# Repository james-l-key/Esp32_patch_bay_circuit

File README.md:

# ESP32 Patch Bay - Hardware

This repository contains the hardware design files for the **ESP32 Patch Bay**, a project for dynamically reconfiguring guitar pedal signal chains. The main firmware repository can be found [here](https://github.com/phi/Esp32_patch_bay).

## Features
- **Schematic**: Designed in KiCad 9.0 (`circuit.kicad_sch`).
- **8-Pedal Support**: The design supports routing for up to 8 mono guitar pedals.
- **Audio Buffering**: Utilizes TL072 op-amps for input and output buffering to maintain signal integrity.
- **Power Isolation**: A TMA-1215D DC/DC converter generates isolated ±15V rails for the analog audio circuitry, ensuring low-noise operation.

## Hardware
The patch bay is built around the following key components:

- **Microcontroller**: ESP32-S3 (e.g., ESP32-S3-WROOM-1 module).
- **Audio Routing**:
  - CD4051B 8-channel analog multiplexers.
  - 3x TL072 dual op-amps for buffering.
- **Control**:
  - 74HC595 8-bit shift registers to control the multiplexers.
- **Power**:
  - The system is powered by a **12V DC** input.
  - Onboard regulators provide **±15V**, **+5V**, **-5V**, and **+3.3V** for all components.

For a complete list of components, please see the **Bill of Materials (BOM)** in the `docs` folder or the `HARDWARE.md` file.

## Power Requirements
- **Input Power**: The system uses an external **24V DC power supply**.
- **Isolated Dual Rails (±15V)**: Supplied by an LM7815 (+15V) and an inverting MC34063AP (-15V)
- **Regulated Rails**: Onboard linear regulators provide stable **+5V**, **-5V**, and **+3.3V** is supplied by the ESP32-s3-Devkit-C for the digital components and ESP32-S3.

## License
This project is licensed under the MIT License. See the [LICENSE](LICENSE) file for details.

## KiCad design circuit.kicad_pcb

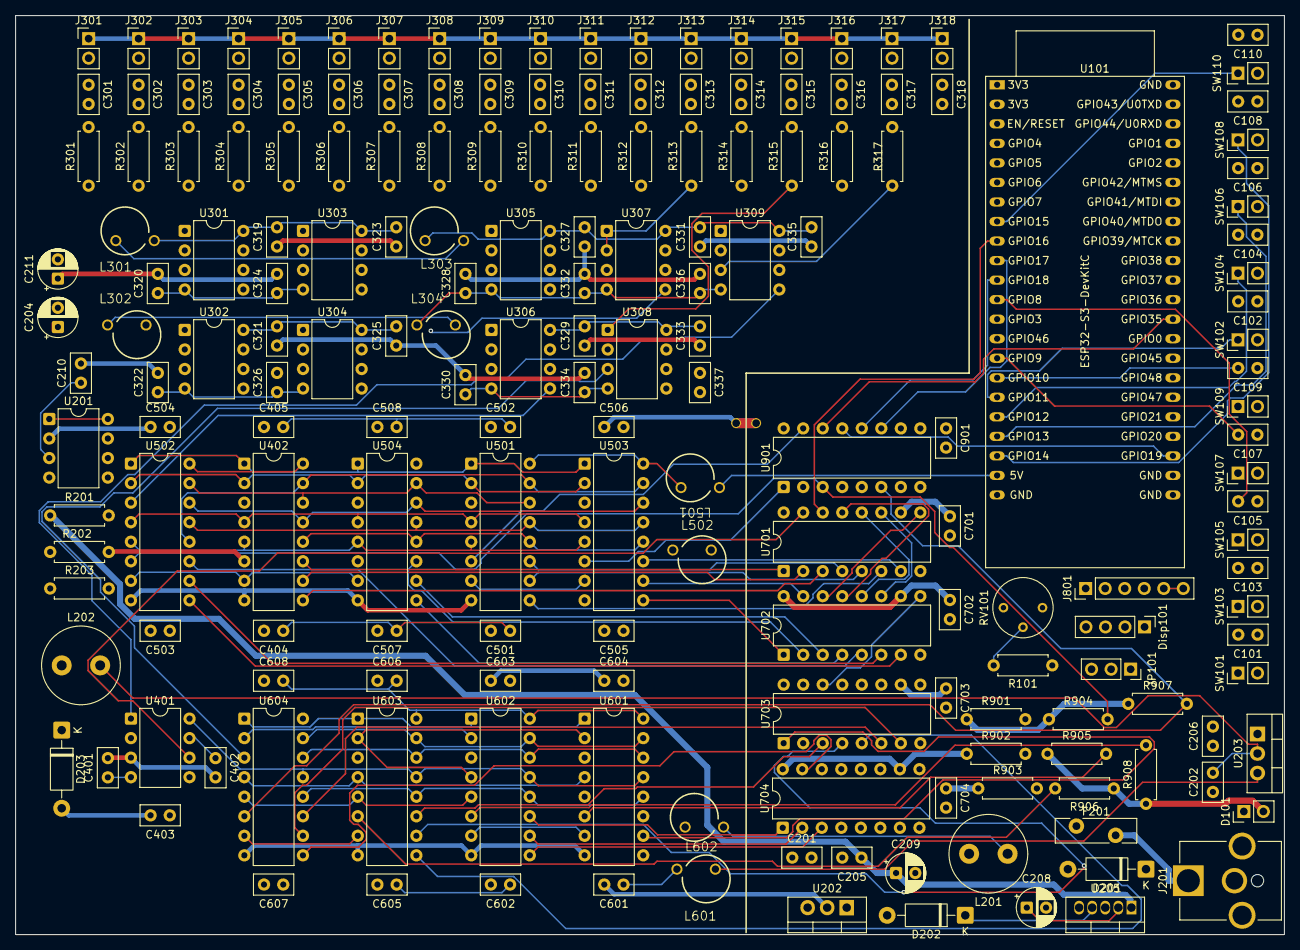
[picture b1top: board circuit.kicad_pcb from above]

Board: 4 copper layers, 165.0 x 119.5 mm, 189 parts (0 on the bottom side), 155 nets.

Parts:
C101, C102, C103, C104, C105, C106, C107, C108, C109, C110, C201, C206, C319, C320, C321, C322, C323, C324, C325, C326, C327, C328, C329, C330, C331, C332, C333, C334, C335, C336, C401, C402, C403, C404, C405, C501, C502, C503, C504, C505, C506, C507, C508, C601, C602, C603, C604, C605, C606, C607, C608, C701, C702, C703, C704, C901: 0.1uF; C_Disc_D5.0mm_W2.5mm_P2.50mm
C202, C205, C301, C302, C303, C304, C305, C306, C307, C308, C309, C310, C311, C312, C313, C314, C315, C316, C317, C318, C337: 1uF; C_Disc_D5.0mm_W2.5mm_P2.50mm
C204, C209, C211: 100uF 50v; CP_Radial_D5.0mm_P2.50mm
C208: 220uF 16v; CP_Radial_D5.0mm_P2.50mm
C210: 470pF; C_Disc_D5.0mm_W2.5mm_P2.50mm
D101: LED_PWR; PinHeader_1x02_P2.54mm_Vertical
D201, D202: 1N5822; D_DO-41_SOD81_P10.16mm_Horizontal
D203: 1N5819; D_DO-41_SOD81_P10.16mm_Horizontal
Disp101: PinHeader_1x04_P2.54mm_Vertical
F201: Polyfuse_Small; Fuse_Bourns_MF-RG500
J201: Barrel_Jack; BarrelJack_CUI_PJ-063AH_Horizontal_CircularHoles
J301: FX_R_1; Jack
J302: FX_R_2; Jack
J303: FX_R_3; Jack
J304: FX_R_4; Jack
J305: FX_R_5; Jack
J306: FX_R_6; Jack
J307: FX_R_7; Jack
J308: FX_R_8; Jack
J309: FX_S_1; Jack
J310: FX_S_2; Jack
J311: FX_S_3; Jack
J312: FX_S_4; Jack
J313: FX_S_5; Jack
J314: FX_S_6; Jack
J315: FX_S_7; Jack
J316: FX_S_8; Jack
J317: Guitar_In; Jack
J318: Amp_Out; Jack
J801: Conn_01x06_Pin; PinHeader_1x06_P2.54mm_Vertical
JP101: Jumper_3_Open; PinSocket_1x03_P2.54mm_Vertical
L201: 150uH; L_Radial_D10.0mm_P5.00mm_Fastron_07M
L202: 220uH; L_Radial_D10.0mm_P5.00mm_Fastron_07M
L301, L302, L303, L304, L501, L502, L601, L602: 600R@100Mhz; WE-UKW_74275010
NT101: NetTie_2; NetTie-2_THT_Pad1.0mm
R101: 100; R_Axial_DIN0207_L6.3mm_D2.5mm_P7.62mm_Horizontal
R201: 1.5; R_Axial_DIN0207_L6.3mm_D2.5mm_P7.62mm_Horizontal
R202: 1k; R_Axial_DIN0207_L6.3mm_D2.5mm_P7.62mm_Horizontal
R203: 11k; R_Axial_DIN0207_L6.3mm_D2.5mm_P7.62mm_Horizontal
R301, R302, R303, R304, R305, R306, R307, R308, R309, R310, R311, R312, R313, R314, R315, R316, R317, R901, R902, R903, R904, R905, R906, R907, R908: 10k; R_Axial_DIN0207_L6.3mm_D2.5mm_P7.62mm_Horizontal
RV101: 500; Potentiometer_Bourns_3339P_Vertical
SW101: Pedal_1; PinHeader_1x02_P2.54mm_Vertical
SW102: Pedal_6; PinHeader_1x02_P2.54mm_Vertical
SW103: Pedal_2; PinHeader_1x02_P2.54mm_Vertical
SW104: Pedal_7; PinHeader_1x02_P2.54mm_Vertical
SW105: Pedal_3; PinHeader_1x02_P2.54mm_Vertical
SW106: Pedal_8; PinHeader_1x02_P2.54mm_Vertical
SW107: Pedal_4; PinHeader_1x02_P2.54mm_Vertical
SW108: Program; PinHeader_1x02_P2.54mm_Vertical
SW109: Pedal_5; PinHeader_1x02_P2.54mm_Vertical
SW110: Preset; PinHeader_1x02_P2.54mm_Vertical
U101: ESP32-S3-DevKitC
U201: MC34063AP; DIP-8_W7.62mm
U202: LM7815_TO220; TO-220-3_Vertical
U203: LM7905_TO220; TO-220-3_Vertical
U205: LM2576HVT-5; TO-220-5_Vertical
U301, U302, U303, U304, U305, U306, U307, U308, U309: TL072; DIP-8_W7.62mm
U401: ADG419BN; DIP-8_W7.62mm
U402, U501, U502, U503, U504, U601, U602, U603, U604: CD4051B; DIP-16_W7.62mm
U701, U702, U703, U704, U901: 74HC595; DIP-16_W7.62mm

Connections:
3.3V: C701.1, C702.1, C703.1, C704.1, C901.1, D101.2 (A), JP101.1 (A), R901.1, R902.1, R903.1, R904.1, R905.1, R906.1, R907.1, R908.1, U101.1 (3V3), U101.2 (3V3), U701.10 (~SRCLR), U701.16 (VCC), U702.10 (~SRCLR), U702.16 (VCC), U703.10 (~SRCLR), U703.16 (VCC), U704.10 (~SRCLR), U704.16 (VCC), U901.10 (~SRCLR), U901.16 (VCC)
5.0V: J801.5, J801.6
+5V: C208.1, JP101.3 (B), L201.1, L501.1, L601.1, U101.21 (5V), U205.2 (OUT)
+5V_F: C403.1, C405.2, C502.2, C504.2, C506.2, C508.2, L501.2, U401.5 (VL), U402.16 (VDD), U501.16 (VDD), U502.16 (VDD), U503.16 (VDD), U504.16 (VDD)
+15V: C201.1, L301.2, L303.1, U202.3 (VO)
+15V_F: C319.2, C321.2, C323.2, C325.2, C401.1, L301.1, U301.8 (V+), U302.8 (V+), U303.8 (V+), U304.8 (V+), U401.4 (V+)
-5V: C206.2, L502.2, L602.2, U203.3 (VO)
-5V_F: C404.1, C501.1, C503.1, C505.1, C507.1, L502.1, U402.7 (VEE), U501.7 (VEE), U502.7 (VEE), U503.7 (VEE), U504.7 (VEE)
-15V: C202.2, C211.2, D203.1 (K), L202.2, L302.1, L304.2, R203.2, U201.1 (SwC), U201.8 (DC), U203.2 (VI)
-15V_F: C320.1, C322.1, C324.1, C326.1, C402.1, L302.2, U301.4 (V-), U302.4 (V-), U303.4 (V-), U304.4 (V-), U401.7 (V-)
/IO Routing/U701_Q0: U401.6, U701.15 (QA)
/IO Routing/U701_Q1: U402.11 (A), U701.1 (QB)
/IO Routing/U701_Q2: U402.10 (B), U701.2 (QC)
/IO Routing/U701_Q3: U402.9 (C), U701.3 (QD)
/IO Routing/U701_Q4: U501.11 (A), U701.4 (QE)
/IO Routing/U701_Q5: U501.10 (B), U701.5 (QF)
/IO Routing/U701_Q6: U501.9 (C), U701.6 (QG)
/IO Routing/U701_Q7: U503.11 (A), U701.7 (QH)
/Inhibit Registers/U901_Q0: R901.2, U501.6 (INH), U901.15 (QA)
/Inhibit Registers/U901_Q1: R902.2, U503.6 (INH), U901.1 (QB)
/Inhibit Registers/U901_Q2: R903.2, U504.6 (INH), U901.2 (QC)
/Inhibit Registers/U901_Q3: R904.2, U502.6 (INH), U901.3 (QD)
/Inhibit Registers/U901_Q4: R905.2, U601.6 (INH), U901.4 (QE)
/Inhibit Registers/U901_Q5: R906.2, U603.6 (INH), U901.5 (QF)
/Inhibit Registers/U901_Q6: R907.2, U604.6 (INH), U901.6 (QG)
/Inhibit Registers/U901_Q7: R908.2, U602.6 (INH), U901.7 (QH)
/Matrix Shift Registers/U702_Q0: U503.10 (B), U702.15 (QA)
/Matrix Shift Registers/U702_Q1: U503.9 (C), U702.1 (QB)
/Matrix Shift Registers/U702_Q2: U504.11 (A), U702.2 (QC)
/Matrix Shift Registers/U702_Q3: U504.10 (B), U702.3 (QD)
/Matrix Shift Registers/U702_Q4: U504.9 (C), U702.4 (QE)
/Matrix Shift Registers/U702_Q5: U502.11 (A), U702.5 (QF)
/Matrix Shift Registers/U702_Q6: U502.10 (B), U702.6 (QG)
/Matrix Shift Registers/U702_Q7: U502.9 (C), U702.7 (QH)
/Matrix Shift Registers/U703_Q0: U601.11 (A), U703.15 (QA)
/Matrix Shift Registers/U703_Q1: U601.10 (B), U703.1 (QB)
/Matrix Shift Registers/U703_Q2: U601.9 (C), U703.2 (QC)
/Matrix Shift Registers/U703_Q3: U603.11 (A), U703.3 (QD)
/Matrix Shift Registers/U703_Q4: U603.10 (B), U703.4 (QE)
/Matrix Shift Registers/U703_Q5: U603.9 (C), U703.5 (QF)
/Matrix Shift Registers/U703_Q6: U604.11 (A), U703.6 (QG)
/Matrix Shift Registers/U703_Q7: U604.10 (B), U703.7 (QH)
/Matrix Shift Registers/U704_Q0: U604.9 (C), U704.15 (QA)
/Matrix Shift Registers/U704_Q1: U602.11 (A), U704.1 (QB)
/Matrix Shift Registers/U704_Q2: U602.10 (B), U704.2 (QC)
/Matrix Shift Registers/U704_Q3: U602.9 (C), U704.3 (QD)
/Power/24V_RAW_1: F201.2, J201.1
/Power/24V_RAW_2: D201.2 (A), F201.1
AGND: C201.2, C204.2, C205.2, C210.2, C211.1, C319.1, C320.2, C321.1, C322.2, C323.1, C324.2, C325.1, C326.2, C327.1, C328.2, C329.1, C330.2, C331.1, C332.2, C333.1, C334.2, C335.1, C336.2, C401.2, C402.2, C403.2, C404.2, C405.1, C501.2, C502.1, C503.2, C504.1, C505.2, C506.1, C507.2, C508.1, C601.2, C602.2, C603.1, C604.1, C605.2, C606.1, C607.2, C608.1, D203.2 (A), J301.S, J302.S, J303.S, J304.S, J305.S, J306.S, J307.S, J308.S, J309.S, J310.S, J311.S, J312.S, J313.S, J314.S, J315.S, J316.S, J317.S, J318.S, L202.1, NT101.2, R202.2, U201.2 (SwE), U201.4 (GND), U202.2 (GND), U401.3 (GND), U402.6 (INH), U402.8 (VSS), U501.8 (VSS), U502.8 (VSS), U503.8 (VSS), U504.8 (VSS), U601.8 (VSS), U602.8 (VSS), U603.8 (VSS), U604.8 (VSS)
FX_R_1: U301.1 (1OUT), U301.2 (1-), U402.13 (X0), U502.14 (X1), U503.14 (X1), U504.14 (X1), U601.14 (X1), U602.14 (X1), U603.14 (X1), U604.14 (X1)
FX_R_2: U301.6 (2-), U301.7 (2OUT), U402.14 (X1), U501.14 (X1), U502.15 (X2), U504.15 (X2), U601.15 (X2), U602.15 (X2), U603.15 (X2), U604.15 (X2)
FX_R_3: U302.1 (1OUT), U302.2 (1-), U402.15 (X2), U501.15 (X2), U502.12 (X3), U503.15 (X2), U601.12 (X3), U602.12 (X3), U603.12 (X3), U604.12 (X3)
FX_R_4: U302.6 (2-), U302.7 (2OUT), U402.12 (X3), U501.12 (X3), U503.12 (X3), U504.12 (X3), U601.1 (X4), U602.1 (X4), U603.1 (X4), U604.1 (X4)
FX_R_5: U303.1 (1OUT), U303.2 (1-), U402.1 (X4), U501.1 (X4), U502.1 (X4), U503.1 (X4), U504.1 (X4), U602.5 (X5), U603.5 (X5), U604.5 (X5)
FX_R_6: U303.6 (2-), U303.7 (2OUT), U402.5 (X5), U501.5 (X5), U502.5 (X5), U503.5 (X5), U504.5 (X5), U601.5 (X5), U602.2 (X6), U604.2 (X6)
FX_R_7: U304.1 (1OUT), U304.2 (1-), U402.2 (X6), U501.2 (X6), U502.2 (X6), U503.2 (X6), U504.2 (X6), U601.2 (X6), U602.4 (X7), U603.2 (X6)
FX_R_8: U304.6 (2-), U304.7 (2OUT), U402.4 (X7), U501.4 (X7), U502.4 (X7), U503.4 (X7), U504.4 (X7), U601.4 (X7), U603.4 (X7), U604.4 (X7)
FX_S_1: U305.3 (1+), U501.3 (X)
FX_S_2: U305.5 (2+), U503.3 (X)
FX_S_3: U306.3 (1+), U504.3 (X)
FX_S_4: U306.5 (2+), U502.3 (X)
FX_S_5: U307.3 (1+), U601.3 (X)
FX_S_6: U307.5 (2+), U603.3 (X)
FX_S_7: U308.3 (1+), U604.3 (X)
FX_S_8: U308.5 (2+), U602.3 (X)
GND: C101.1, C102.1, C103.1, C104.1, C105.1, C106.1, C107.1, C108.1, C109.1, C110.1, C202.1, C206.1, C208.2, C209.2, C701.2, C702.2, C703.2, C704.2, C901.2, D202.2 (A), Disp101.4 (GND), J201.2, J801.1, NT101.1, RV101.3, SW101.2, SW102.2, SW103.2, SW104.2, SW105.2, SW106.2, SW107.2, SW108.2, SW109.2, SW110.2, U101.22 (GND), U101.23 (GND), U101.24 (GND), U101.44 (GND), U203.1 (GND), U205.3 (GND), U205.5 (~ON/OFF), U701.8 (GND), U702.8 (GND), U703.8 (GND), U704.8 (GND), U901.8 (GND)
GUITAR_IN: C337.2, U401.8, U501.13 (X0), U502.13 (X0), U503.13 (X0), U504.13 (X0), U601.13 (X0), U602.13 (X0), U603.13 (X0), U604.13 (X0)
INHIBIT_SR_DS: U101.32 (GPIO35), U901.14 (SER)
MATRIX_OUT_PRE: U309.5 (2+), U401.1
MATRIX_SR_DS: U101.9 (GPIO16/ADC2_CH5/32K_N), U701.14 (SER)
unnamed: C301.1, J301.T
unnamed: C301.2, R301.2
unnamed: C302.1, J302.T
unnamed: C302.2, R302.2
unnamed: C303.1, J303.T
unnamed: C303.2, R303.2
unnamed: C304.1, J304.T
unnamed: C304.2, R304.2
unnamed: C305.1, J305.T
unnamed: C305.2, R305.2
unnamed: C306.1, J306.T
unnamed: C306.2, R306.2
unnamed: C307.1, J307.T
unnamed: C307.2, R307.2
unnamed: C308.1, J308.T
unnamed: C308.2, R308.2
unnamed: C309.1, J309.T
unnamed: C309.2, R309.2
unnamed: C310.1, J310.T
unnamed: C310.2, R310.2
unnamed: C311.1, J311.T
unnamed: C311.2, R311.2
unnamed: C312.1, J312.T
unnamed: C312.2, R312.2
unnamed: C313.1, J313.T
unnamed: C313.2, R313.2
unnamed: C314.1, J314.T
unnamed: C314.2, R314.2
unnamed: C315.1, J315.T
unnamed: C315.2, R315.2
unnamed: C316.1, J316.T
unnamed: C316.2, R316.2
unnamed: C317.1, J317.T
unnamed: C317.2, R317.2
unnamed: C318.1, J318.T
unnamed: D101.1 (K), R101.1
unnamed: D202.1 (K), L201.2, U205.4 (FB)
unnamed: Disp101.1 (VCC), JP101.2 (C)
unnamed: R101.2, RV101.2
unnamed: C101.2, SW101.1, U101.6 (GPIO6/ADC1_CH5)
unnamed: C103.2, SW103.1, U101.7 (GPIO7/ADC1_CH6)
unnamed: C105.2, SW105.1, U101.12 (GPIO8/ADC1_CH7)
unnamed: C107.2, SW107.1, U101.15 (GPIO9/ADC1_CH8)
unnamed: C109.2, SW109.1, U101.16 (GPIO10/ADC1_CH9)
unnamed: C102.2, SW102.1, U101.17 (GPIO11/ADC2_CH0)
unnamed: C104.2, SW104.1, U101.18 (GPIO12/ADC2_CH1)
unnamed: C106.2, SW106.1, U101.19 (GPIO13/ADC2_CH2)
unnamed: C108.2, SW108.1, U101.20 (GPIO14/ADC2_CH3)
unnamed: C110.2, SW110.1, U101.8 (GPIO15/ADC2_CH4/32K_P)
unnamed: R201.2, U201.7 (Ipk)
unnamed: C210.1, U201.3 (TC)
unnamed: R202.1, R203.1, U201.5 (Vfb)
unnamed: R301.1, U301.3 (1+)
unnamed: R302.1, U301.5 (2+)
unnamed: R303.1, U302.3 (1+)
unnamed: R304.1, U302.5 (2+)
unnamed: R305.1, U303.3 (1+)
unnamed: R306.1, U303.5 (2+)
unnamed: R307.1, U304.3 (1+)
unnamed: R308.1, U304.5 (2+)
unnamed: R309.1, U305.1 (1OUT), U305.2 (1-)
unnamed: R310.1, U305.6 (2-), U305.7 (2OUT)
unnamed: C327.2, C329.2, C331.2, C333.2, C335.2, L303.2, U305.8 (V+), U306.8 (V+), U307.8 (V+), U308.8 (V+), U309.8 (V+)
unnamed: C328.1, C330.1, C332.1, C334.1, C336.1, L304.1, U305.4 (V-), U306.4 (V-), U307.4 (V-), U308.4 (V-), U309.4 (V-)
unnamed: R311.1, U306.1 (1OUT), U306.2 (1-)
unnamed: R312.1, U306.6 (2-), U306.7 (2OUT)
unnamed: R313.1, U307.1 (1OUT), U307.2 (1-)
unnamed: R314.1, U307.6 (2-), U307.7 (2OUT)
unnamed: R315.1, U308.1 (1OUT), U308.2 (1-)
unnamed: R316.1, U308.6 (2-), U308.7 (2OUT)
unnamed: R317.1, U309.3 (1+)
unnamed: C337.1, U309.1 (1OUT), U309.2 (1-)
unnamed: C318.2, U309.6 (2-), U309.7 (2OUT)
unnamed: U401.2, U402.3 (X)
unnamed: C603.2, C604.2, C606.2, C608.2, L601.2, U601.16 (VDD), U602.16 (VDD), U603.16 (VDD), U604.16 (VDD)
unnamed: C601.1, C602.1, C605.1, C607.1, L602.1, U601.7 (VEE), U602.7 (VEE), U603.7 (VEE), U604.7 (VEE)
unnamed: U701.9 (QH'), U702.14 (SER)
unnamed: U702.9 (QH'), U703.14 (SER)
unnamed: U703.9 (QH'), U704.14 (SER)
SCL: Disp101.3 (SCL), J801.3, U101.5 (GPIO5/ADC1_CH4)
SDA: Disp101.2 (SDA), J801.4, U101.4 (GPIO4/ADC1_CH3)
SR_OE: U101.25 (GPIO19/USB_D-), U701.13 (~OE), U702.13 (~OE), U703.13 (~OE), U704.13 (~OE), U901.13 (~OE)
SR_SHCP: U101.10 (GPIO17/ADC2_CH6), U701.11 (SRCLK), U702.11 (SRCLK), U703.11 (SRCLK), U704.11 (SRCLK), U901.11 (SRCLK)
SR_STCP: U101.11 (GPIO18/ADC2_CH7), U701.12 (RCLK), U702.12 (RCLK), U703.12 (RCLK), U704.12 (RCLK), U901.12 (RCLK)
VIN_24V: C204.1, C205.1, C209.1, D201.1 (K), R201.1, U201.6 (Vin), U202.1 (VI), U205.1 (VIN)

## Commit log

2025-06-16 Initial commit for new subrepo
2025-06-17 Create LICENSE
2025-06-17 New cooler (thermally) power supply.
2025-06-21 Removed un-needed inhibit from amp out. thereby simplifying the shift registers.
2025-06-21 merge
2025-06-21 Fixed corrupt merge
2025-06-21 Removed LED Shift registers and replaced them with PCA9685 PWM controllers, Also changed LEDs to RGB LEDs.
2025-06-21 pre-merge
2025-06-22 Added Datasheets and specified polyfuse parameters.
